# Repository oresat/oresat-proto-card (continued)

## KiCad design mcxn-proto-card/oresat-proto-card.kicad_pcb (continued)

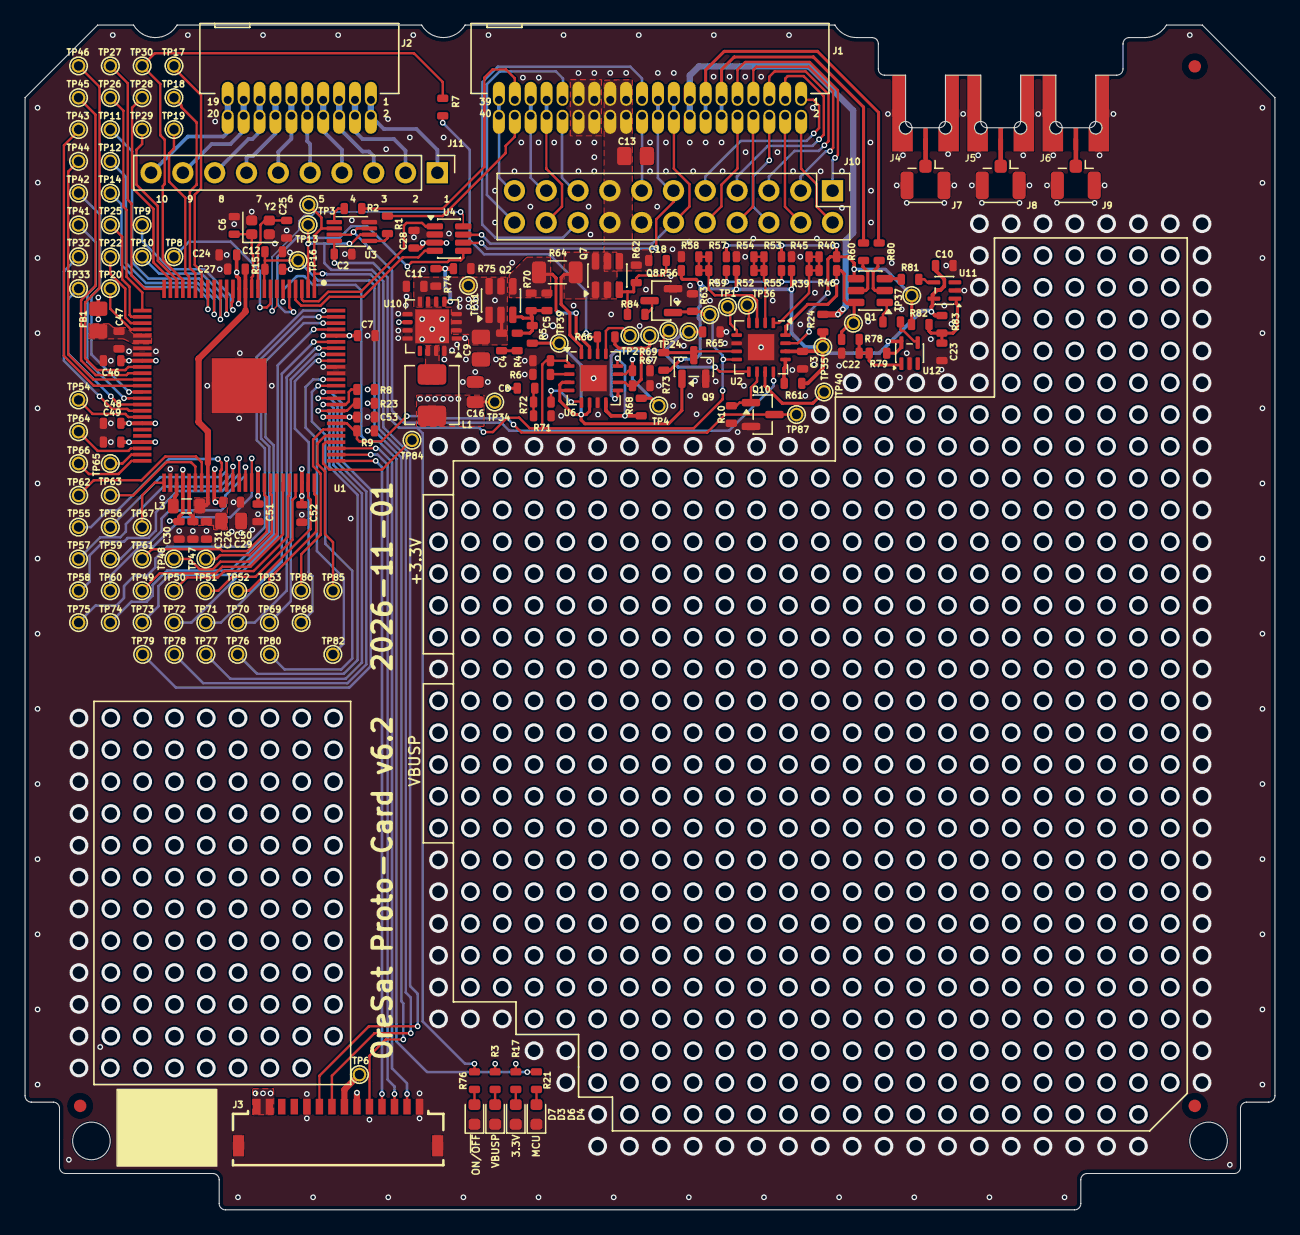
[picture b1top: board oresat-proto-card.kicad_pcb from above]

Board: 4 copper layers, 99.8 x 94.6 mm, 205 parts (0 on the bottom side), 169 nets.

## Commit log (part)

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2017-09-20 First cut at a protoboard for OreSat.
2017-09-21 Finished protocard layout.
2017-09-21 now with 300% more LEDs!
2017-09-22 Add a pic!
2017-09-22 Oh shoot I forgot text labels. K is going to hate me even more. Well, too late. Ready for v1.1!
2017-09-22 Better smaller pic
2017-09-25 EAGLE 7 files for Austin.
2017-09-28 Minor changes, mostly massaging.
2017-10-01 Still v1.1, but lots of changes! Moved spare lines over, added way more prototyping area, flipped around STM32 to save room, and added 3 MMCX connectors with U.FL breakouts so that we can hook up ext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
2017-10-02 Took K's suggestion: added mounting holes (not necessary in OreSat cards, but whatever) and a FTDI breakout connector. Oh, and stitched some more, and cleaned up silkscreen.
2018-01-10 Updated some net names to reflect SPI bus. Actual useful BOM now.
2018-03-06 Rough draft of the OreSat Prototype Card v2.0! Done, awaiting stapling, TNAMES checking, polish, and feedback from Miles that everything works as expected :)
2018-03-09 Renamed CAN transceiver lines.
2018-03-13 Now with correctly positioned main connector, 100% more auxiliary connectors, and less silly double row headers to make room for it all.
2018-03-13 Removed stupid layers.
2018-03-13 Added DXF import of card outline and keepouts via DXF into the REFERENCE layer. Moved bottom connectors to get out of the way of the fingers from the +X side.
2018-03-13 Added some attributes.
2018-03-13 Cleaned up ERC, changed VBAT to VBUS label.
2018-09-11 Changes for the OreSat Backplane v1.0! Now with 100% more SMPM connectors.
2018-09-11 Recovered BOM which was deleted for some reason. BOM is NOT updated! Needs work.
2018-09-11 Updated protocard documentation.
2018-09-25 Removing GPL v3; moving to CERN OHL.
2018-09-25 Changed to CERN OHL v1.2.
2018-11-22 v3 protocard. Works with current 2018/11/22 structure.
2018-11-22 Update documentation to the latest.
2018-11-22 Huh, image didn't work. Fixed.
2018-11-22 Fixed table.
2018-11-26 minor tweaks, including fixing power supply resistors.
2019-02-10 Uh. Yeah. Well, it wasn't my fault, I blame Oliver J. Power domain circuitry now figured out from a topology point of view. Lots of changes to the power front end, and the main and aux connctors. Als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
2019-02-10 Cleaned up TNAMES layer.
2019-02-10 More schematic and board polishing. Went over ERCs and DRCs, some layout polishing, more ground stitching.
2019-02-11 More board and schematic polishing. Swapped SWD connector with SMT version for easy removal. Added more test points on the MAX7210 power domain controller.
2019-02-25 Latest OreSat protocard, version 3.1, with updated BOM, and design notes!
2019-02-25 Ugggh digikey made me add their part numbers. Hrmph.
2019-02-27 Added OreSat power domain -- via design blocksgit status -- and OMG it's doneish.
2019-02-27 OMG next time check which repo you're in. Reverting the last commit and push.
2019-03-27 Added new safety circuit on the I2C of the OPD.
2019-05-22 Latest card outline from Ryan and Catie, and added the first OPD protection circuit revision.
2019-06-24 uploading very early octavo protocard stuff
2019-07-09 Made note of error in circuit breaker to be fixed at a later date
2019-07-17 flipped comparator inputs on circuit breaker
2019-07-18 updated m0 protocard to include I2C breaker CAD and added more stitching
2019-07-18 removed TODO note
2019-07-20 added datasheets for m0
2019-07-29 last minute drc fixes
2019-07-29 fixed airwire
2019-07-30 added capablity for M0 bootstrapping over OPD I2C bus. Added extra ground plane stitching. Replaced some previously removed prototyping area
2019-07-31 moved some stitching around
2019-08-03 Final cleanup on the v3.2 protocard. Moved tall components away from the +X end of things because of the new slopes on the +X frame, and added two resistors on the OPD I2C bootloader gambit because w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
2019-08-04 OMG that was close: Changes to main pinout in Backplane v2.1 did not get updated in protocard. Fixed.
2019-08-04 flatsat breakout boards, one for main, one for aux, connectors.
2019-08-04 More notes after talking with David, changed I2C bootloader resistor values, and fixed AUX conector signal names.
2019-08-05 Moved in +X squeezy ends by 0.15 mm on both sides.
2019-08-05 Reduce all vias to 0.254 mm.
2019-08-05 TPLACE cleaup.
2019-08-12 added todo on protocard to connect Iout and Pout to M0
2019-08-20 "auto-generated from update_repos.py"
2019-08-25 added test point on the nreset line
2019-08-25 added test point to cb_ctrl
2019-09-02 added test points and updated manufacturing image
2019-09-04 added SPICE simulations for the I2C protection circuit
2019-09-16 updates to OPD, new I2C protection circuit
2019-09-28 Added new I2C protection, connected Pout to M0 through 10k
2019-10-29 added board layout of new I2C protection circuit
2019-10-29 stray airwire
2019-12-07 fixed j-tag connect, final tweaks for 3.3, updated bom
2019-12-17 Now v3.3. New OPD I2C protection circuits. Move to 4 layers. Lots of cleanup and massaging, but nothing worth saying. Added ground ring around 3.3V ring on L15. Attributes are still wrong, needs to b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
2019-12-20 Removed lockfile. Nice one, David.
2019-12-20 fixing the lock?
2019-12-20 organization house keeping
2019-12-23 Fixed MIC842L flipped pins. Layout turned out to be better, too!
2020-02-27 Added card debug board
    20 pin ffc edge connector debug board
2020-02-27 Design and layout notes For Debug board
2020-02-27 Added lables, diff pairs , GND vias
2020-02-28 Added P Channel MOSFET switched VUSB
    Made Voltage buses wider
2020-02-28 Added jumper select for Host5V or Debug-0
2020-02-28 Clear stubs and DRC errors
2020-02-28 clear all ERC errors
2020-02-28 Push For Review
2020-02-28 Minor fixes
    Added labels
2020-02-29 Design review changes made
2020-03-03 Made changes per design review
    Added test points for RX TX rewire, made board smaller
2020-03-16 Added masking for TX and RX
2020-03-25 Changed from VBUSP to VBUS for power out
2020-04-14 Swapped TX RX traces
2020-04-14 updated the pin connectors
2020-04-20 Version 1 of the OreSat debug board. Tinyified the board, added curved corners, centered FFC connector, added reset switch, made USB traces have a continuous ground plane, fixed FT203x VCCIO connecti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
2020-04-27 Renamed VBUS to VBUSP added attributes to make BOM
2020-04-27 Completed Version 1 BOM for connector board
2020-05-24 Re-Done with mirrored edge connector
2020-05-24 Clean up text , added gnd via's
2020-06-21 protocard preliminary rev 3.5
2020-06-22 new stm dbl, new programming connector, minor layout tweaks
2020-06-25 swapped 0402 to 0603 where necessary, fixed labels on tnames layer
2020-06-28 updated design blocks, got rid of unneeded breakouts
2020-06-28 Polishing to the schematic only; ready for v4! Still needs layout polishing.
2020-06-29 Switched to thin mirrored edge connector
2020-06-29 moved ffc to bottom of card, fixed silkscreen, moved and expanded Vbus and 3.3V breakouts
2020-06-30 minor tweak to ground plane stitching
2020-07-06 Added jumper and diode for 3.0V supply for solar for debugging without solar power.
2020-07-06 fixed an error where Pout was not routed to an ADC pin
2020-07-20 Minor DRC clean up, fixed 3.3V plane cut by VBUSP, and some TSTOPs being too close.
2020-07-20 Minor erc and drc cleanup.
2020-07-22 updated attributes and BOM
2020-08-09 Added 10k resistor to the FTDI's TXD line so that we don't accidentally power the card through the transmit line)
2020-08-09 Fixed RX/TX screw up (updated debug connector).
2020-08-10 Updated to 4.1: switched to better debug connector, fixed OPD capacitance problem.
2020-08-10 Oh right and fix the I2C pullups to 4.7k
2020-12-02 Added 10 uF cap after on/off P channel switch, and added values to MAX4311 inhibit RC circuitr, all to prevent accidental trips.
2020-12-02 Added MAX4311 inhibit RC filter calculations.
2021-08-22 Moved design notes to a google document, and linked it.
2021-08-29 Moved debug and card breakouts to the oresat-flatsat repo.
2021-10-31 Fixed a handful of misc Git issues. Started KiCAD import of protocard V4.1
2021-11-09 moved files to f0-proto-card folder
2021-11-11 imported oresat-live-card Eagle project to KiCAD 5.99. Moved oresat-proto-card files to f0-proto-card directory
2021-11-15 removed page 6; edited connectors, PWR and SD reader schematic
2024-02-09 Updated proto card to new board outline and backplane pinout. Moved to KiCAD
2024-02-25 Some design review changes for protocard v5.0
2024-02-25 Finished cleaning up protocard
2024-03-22 Starting to correctly name all the protocards
2024-03-22 Latest .gitignore file
2024-03-22 Removed temporary files that shouldn't have been committed.
2024-03-22 More cleanup, and renaming of files, and better page layout
2025-06-29 Set up new folder for MCXN version of the protocard
2025-06-30 Replaced J1 and JP9 w/ OreSat library equivalent
2025-06-30 Removed and replaced eagle libraries for C, R, and Power symbols
2025-07-02 Removed and replaced Eagle libraries for MOSFET
2025-07-03 Eagle libraries removed and replaced, schematic and layout clean up
2025-07-08 Eagle libraries replaced, scheatic and layout clean up cont.
2025-07-08 Cleaned up layout and routing
2025-07-08 Updated TPS62111RSA
2025-07-09 changed layout
2025-07-11 Fixed linked library footprints and routing
2025-07-12 Fixed schematic and routing for 2x11 connector
2025-07-14 Fixed some minor ERC and DRC errors
2025-11-19 Fully routed MCXN947 proto card, still needs final polish.
    Big cleanup of the proto card's OPD, bringing it up to modern standards. Also fixed the v2 backplane connector. Added the MCXN937 processor, and breakouts for the unused pins. Switched to the new deb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
2025-12-29 Final MCXN protocard cleanup
    Made schematic fancy with hierarchical pins, cleaned up schematics a bit, and fixed silk screen a ton. Ready for fab.
2025-12-29 Fab v6.0 proto-card
2025-12-30 BOM fixed; schematic polish (no change to PCB v6.0)
    Fixed BOM, and synced with OreSat BOMs Google Sheet. Figured out large capacitor (> 4.7u) voltages and package issues, which are many. Set MCXN pin names to the right selection if possible.
2025-12-30 Small schematic aesthetics, no change to sch or pcb.
2026-06-28 Update protocard
    Update to 10.0.4, new .gitignore, better hierachical layout, updated footprints, re-arranged LEDs, brought outline and SMPMs into latest standards, all but OPD is updated.
2026-06-29 Small cleanups for manufacturing
